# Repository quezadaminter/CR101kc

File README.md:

# CR101kc
The electrical schematics and PCB layout for the CR101 boards.  

# Firmware  
https://github.com/quezadaminter/CR101fw  

# User code  
https://github.com/quezadaminter/CR101py

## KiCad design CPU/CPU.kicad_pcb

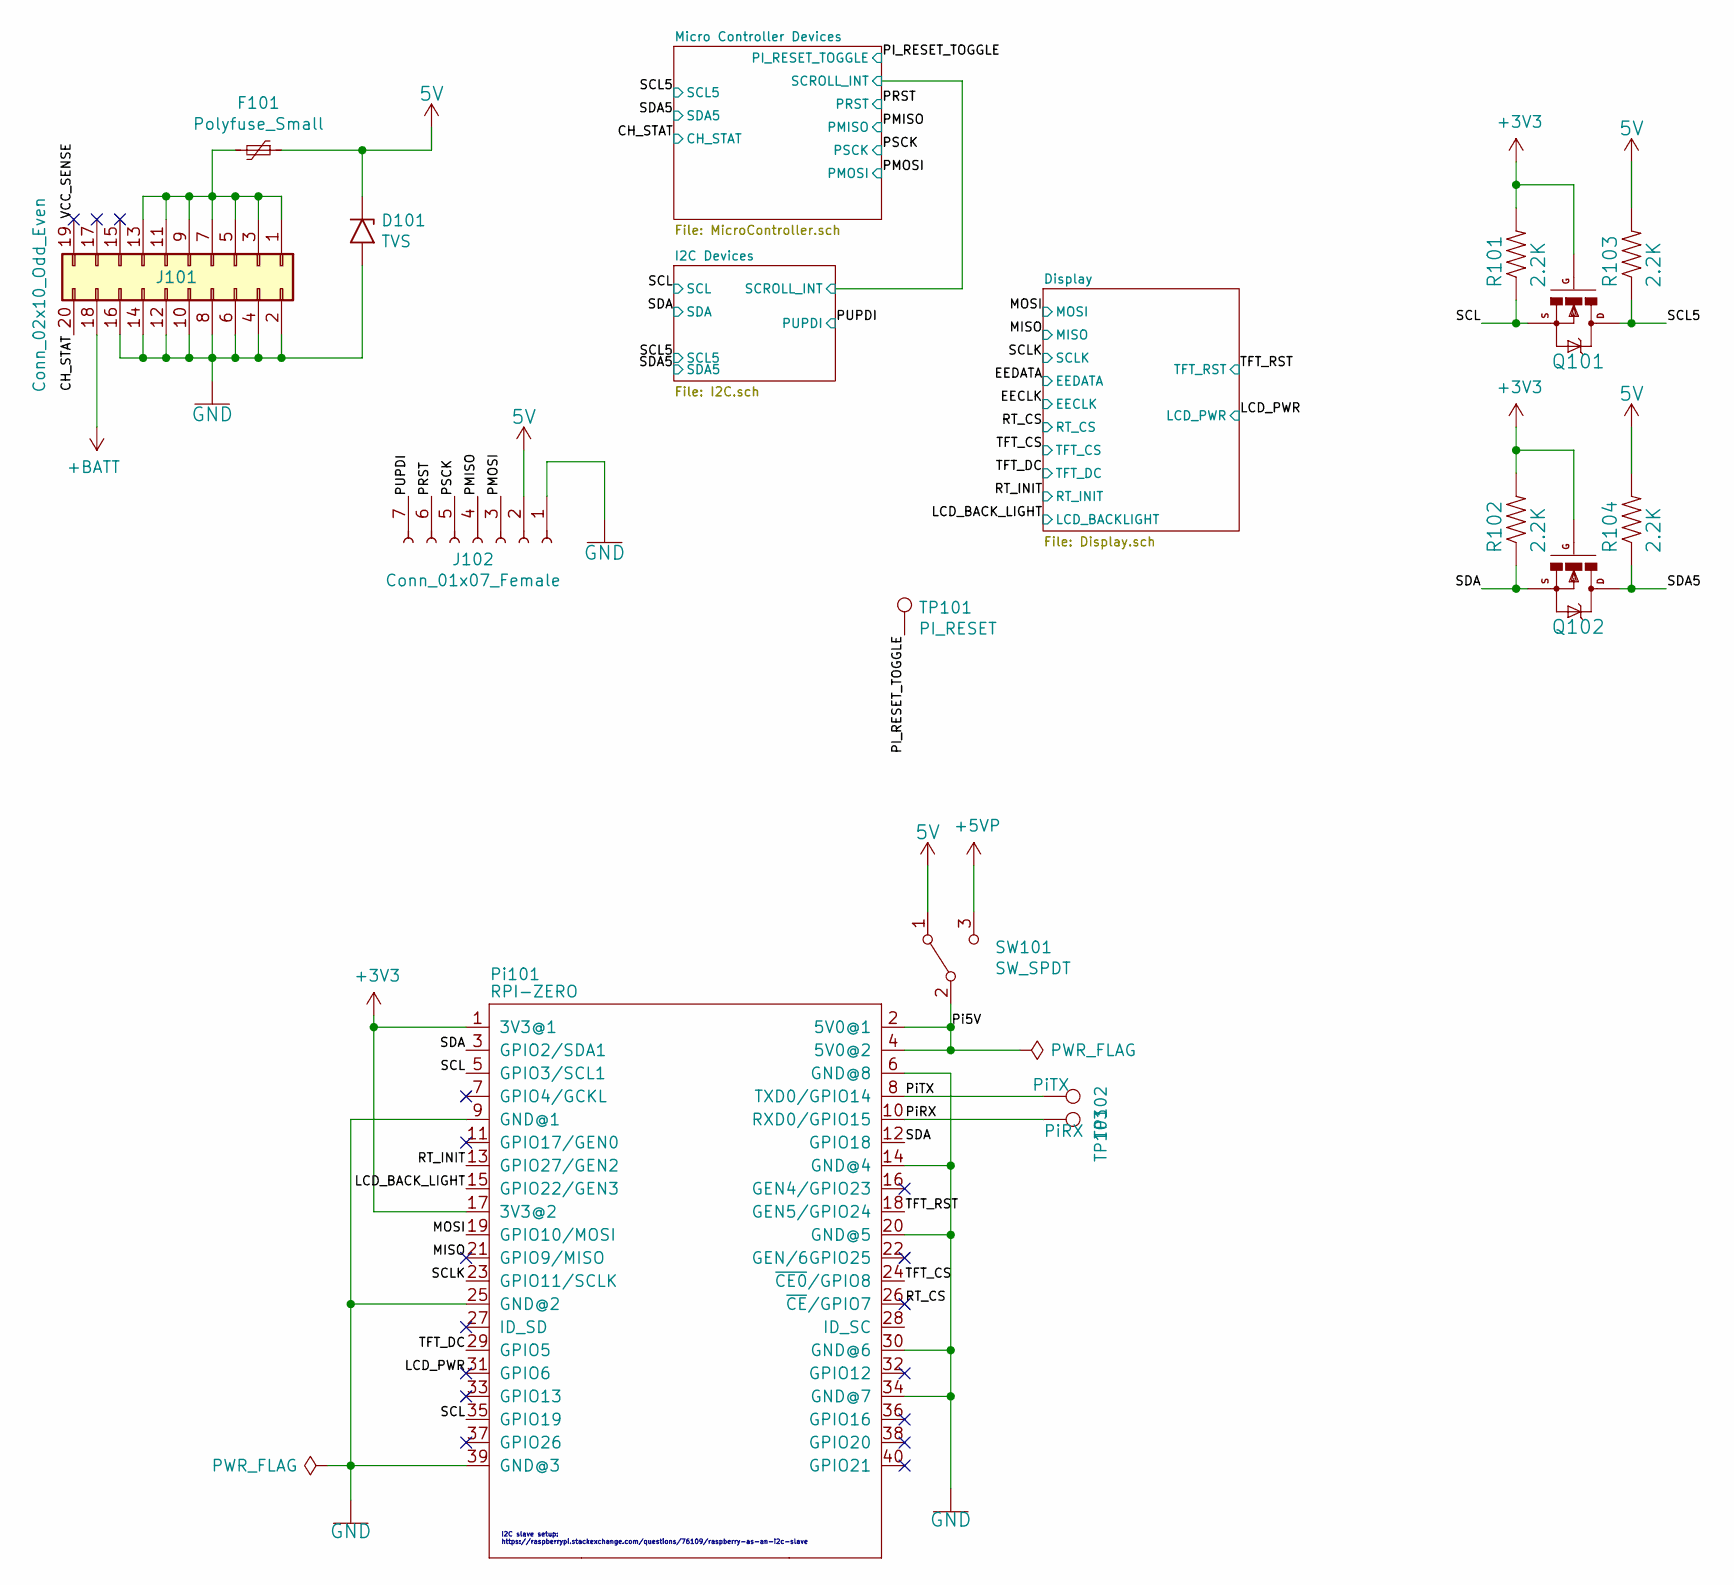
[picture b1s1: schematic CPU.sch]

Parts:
D101: TVS; D_SMB-SMC_Universal_Handsoldering; DigiKey SMBJ5V0A
F101: Polyfuse_Small; Fuse_1210_3225Metric_Pad1.42x2.65mm_HandSolder; DigiKey PTSLR12066V110
J101: Conn_02x10_Odd_Even; PinHeader_2x10_P2.00mm_Vertical_SMD; LCSC Part Number C135211
J102: Conn_01x07_Female; SM07B-SHLS-TF; DigiKey SM07B-SHLS-TF(LF)(SN)
Pi101: RPI-ZERO; RASPBERRYPI_Zero-No_Mounting_Holes_SMD_Flat; DigiKey 609-2231-ND
Q101, Q102: IRLML0040TR; SOT23; LCSC Part Number C67273
R101, R102, R103, R104: 2.2K; R_0805_2012Metric_Pad1.15x1.40mm_HandSolder; LCSC Part Number C17520
SW101: SW_SPDT; SWITCH_SS312SAH4_SPDT; LCSC Part Number C221841
TP101: PI_RESET; TestPoint_Pad_D1.0mm
TP102: PiTX; TestPoint_Pad_D1.0mm
TP103: PiRX; TestPoint_Pad_D1.0mm

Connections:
5V: D101.1 (A1), F101.1, J102.2, R103.2, R104.2, SW101.1 (A); also elsewhere on the board
+3V3: Pi101.1 (3V3@1), Pi101.17 (3V3@2), Q101.1 (G), Q102.1 (G), R101.2, R102.2; also elsewhere on the board
+5VP: SW101.3 (C); also elsewhere on the board
+BATT: J101.18; also elsewhere on the board
/CH_STAT: J101.20; also elsewhere on the board
/LCD_BACK_LIGHT: Pi101.15 (GPIO22/GEN3); also elsewhere on the board
/LCD_PWR: Pi101.31 (GPIO6)
/MISO: Pi101.21 (GPIO9/MISO)
/MOSI: Pi101.19 (GPIO10/MOSI); also elsewhere on the board
/PI_RESET_TOGGLE: TP101.1; also elsewhere on the board
/PMISO: J102.4; also elsewhere on the board
/PMOSI: J102.3; also elsewhere on the board
/PRST: J102.6; also elsewhere on the board
/PSCK: J102.5; also elsewhere on the board
/PUPDI: J102.7; also elsewhere on the board
/Pi5V: Pi101.2 (5V0@1), Pi101.4 (5V0@2), SW101.2 (B)
/PiRX: Pi101.10 (RXD0/GPIO15), TP103.1
/PiTX: Pi101.8 (TXD0/GPIO14), TP102.1
/RT_CS: Pi101.26 (~CE~/GPIO7)
/RT_INIT: Pi101.13 (GPIO27/GEN2)
/SCL: Pi101.5 (GPIO3/SCL1), Pi101.35 (GPIO19), Q101.2 (S), R101.1; also elsewhere on the board
/SCL5: Q101.3 (D), R103.1; also elsewhere on the board
/SCLK: Pi101.23 (GPIO11/SCLK); also elsewhere on the board
/SDA: Pi101.3 (GPIO2/SDA1), Pi101.12 (GPIO18), Q102.2 (S), R102.1; also elsewhere on the board
/SDA5: Q102.3 (D), R104.1; also elsewhere on the board
/TFT_CS: Pi101.24 (~CE0~/GPIO8); also elsewhere on the board
/TFT_DC: Pi101.29 (GPIO5); also elsewhere on the board
/TFT_RST: Pi101.18 (GEN5/GPIO24); also elsewhere on the board
/VCC_SENSE: J101.19
GND: D101.2 (A2), J101.2, J101.4, J101.6, J101.8, J101.10, J101.12, J101.14, J101.16, J102.1, Pi101.6 (GND@8), Pi101.9 (GND@1), Pi101.14 (GND@4), Pi101.20 (GND@5), Pi101.25 (GND@2), Pi101.30 (GND@6), Pi101.34 (GND@7), Pi101.39 (GND@3); also elsewhere on the board
unnamed: F101.2, J101.1, J101.3, J101.5, J101.7, J101.9, J101.11, J101.13

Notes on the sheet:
I2C slave setup: https://raspberrypi.stackexchange.com/questions/76109/raspberry-as-an-i2c-slave

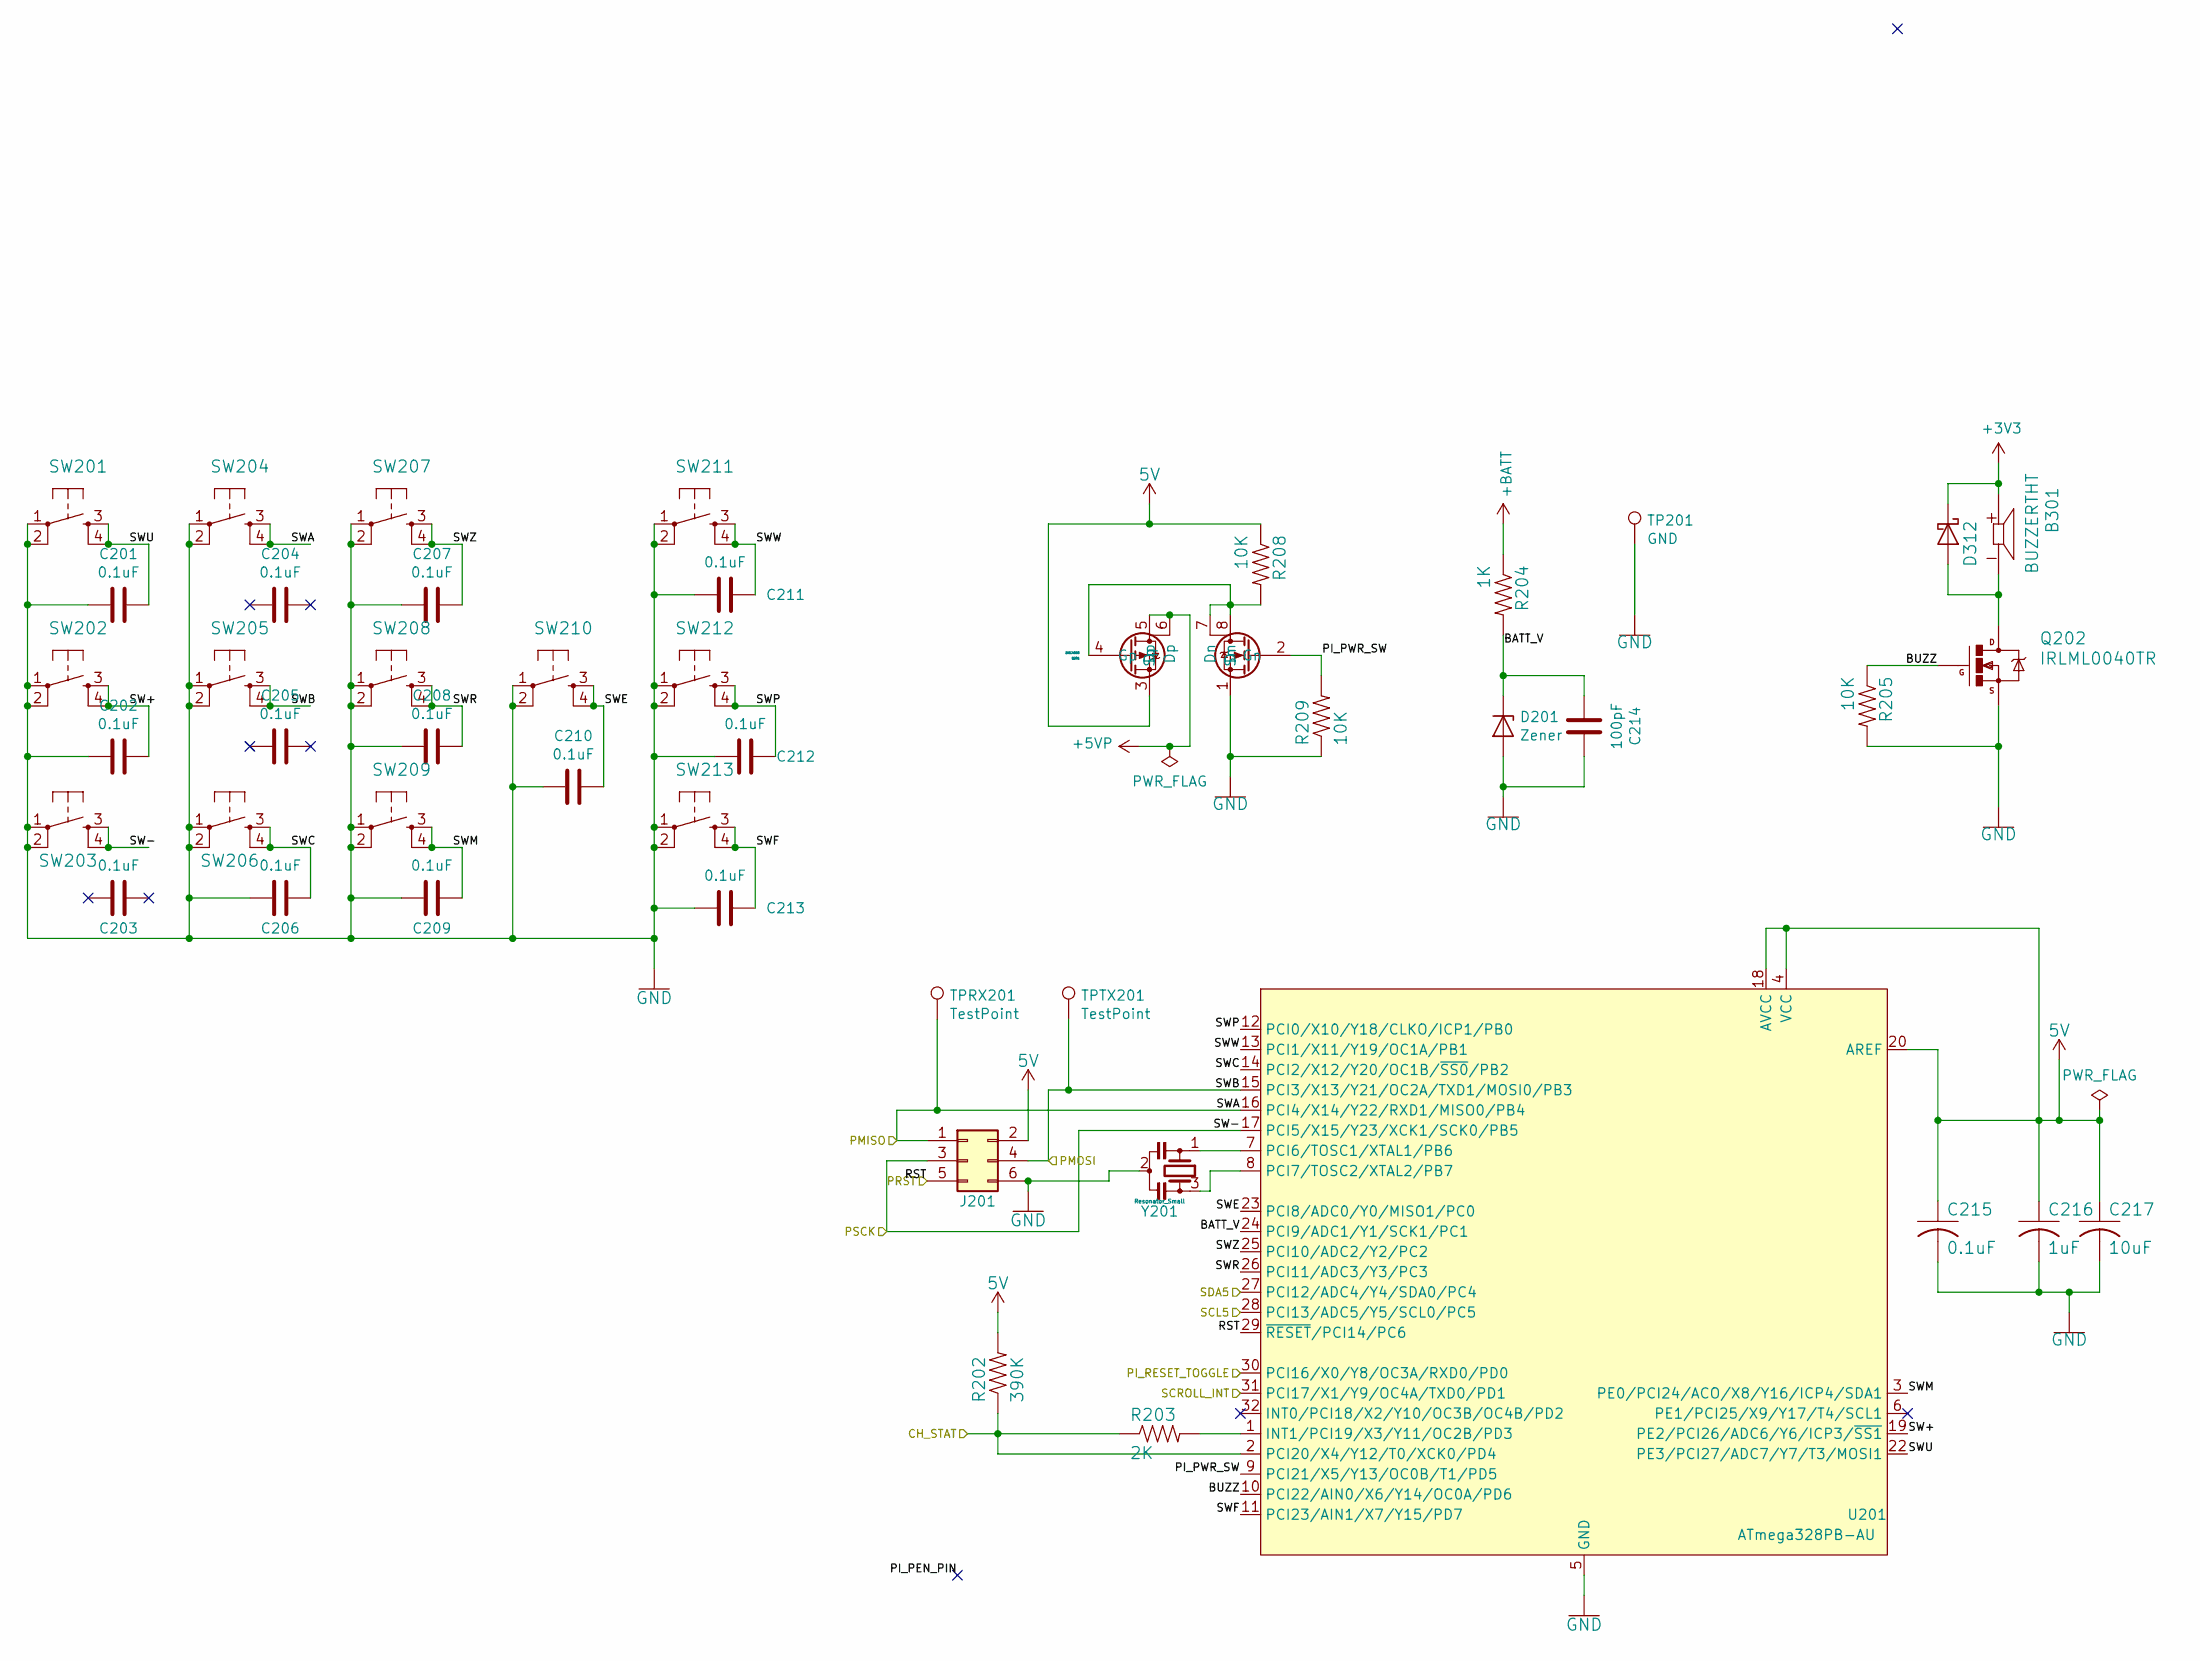
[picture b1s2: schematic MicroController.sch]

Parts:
B301: BUZZERTHT; XDCR_CMT-0904-85T; DigiKey CMT-0904-85T
C201, C202, C203, C204, C205, C206, C207, C208, C209, C210, C211, C212, C213, C215: 0.1uF; C_0805_2012Metric_Pad1.15x1.40mm_HandSolder; LCSC Part Number C49678
C214: 100pF; C_0805_2012Metric_Pad1.15x1.40mm_HandSolder; LCSC Part Number C1790
C216: 1uF; C_0805_2012Metric_Pad1.15x1.40mm_HandSolder; LCSC Part Number C28323
C217: 10uF; C_0805_2012Metric_Pad1.15x1.40mm_HandSolder; LCSC Part Number C15850
D201: Zener; D_0805_2012Metric_Pad1.15x1.40mm_HandSolder; DigiKey UDZVFHTE-174.7BCT-ND
D312: DIODE; MICRO_SMP; LCSC Part Number C111315
J201: Conn_02x03_Odd_Even; PinHeader_2x03_P2.54mm_Vertical; DigiKey 818-22-006-10-002101
Q201: DMC4050; SO-8_3.9x4.9mm_P1.27mm; DigiKey DMC4050SSD-13
Q202: IRLML0040TR; SOT23; LCSC Part Number C67273
R202: 390K; R_0805_2012Metric_Pad1.15x1.40mm_HandSolder; LCSC Part Number C17656
R203: 2K; R_0805_2012Metric_Pad1.15x1.40mm_HandSolder; LCSC Part Number C17604
R204: 1K; R_0805_2012Metric_Pad1.15x1.40mm_HandSolder; LCSC Part Number C17513
R205, R208, R209: 10K; R_0805_2012Metric_Pad1.15x1.40mm_HandSolder; LCSC Part Number C17414
SW201, SW202, SW203, SW204, SW205, SW206, SW207, SW208, SW209, SW210, SW211, SW212, SW213: TACTILE_SWITCHPTS540-SMD; PTS540-ULTRA_LOW_PROFILE_SW_SPST; LCSC Part Number C221864
TP201: GND; TestPoint_Pad_4.0x4.0mm
TPRX201: TestPoint; TestPoint_Pad_D2.0mm
TPTX201: TestPoint; TestPoint_Pad_D2.0mm
U201: ATmega328PB-AU; TQFP-32_7x7mm_P0.8mm; LCSC Part Number C132230
Y201: Resonator_Small; Resonator_SMD_muRata_CSTxExxV-3Pin_3.0x1.1mm_HandSoldering; DigiKey CSTNE20M0VH3L000R0

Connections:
5V: C215.1, C216.1, C217.1, J201.2, Q201.3 (Sp), R202.2, R208.1, U201.4 (VCC), U201.18 (AVCC), U201.20 (AREF); also elsewhere on the board
+3V3: B301.P, D312.1 (K); also elsewhere on the board
+5VP: Q201.5 (Dp), Q201.6 (Dp); also elsewhere on the board
+BATT: R204.1; also elsewhere on the board
/CH_STAT: R202.1, R203.1, U201.2 (PCI20/X4/Y12/T0/XCK0/PD4); also elsewhere on the board
/I2C Devices/SCROLL_INT: U201.31 (PCI17/X1/Y9/OC4A/TXD0/PD1); also elsewhere on the board
/Micro Controller Devices/BATT_V: C214.1, D201.1 (K), R204.2, U201.24 (PCI9/ADC1/Y1/SCK1/PC1)
/Micro Controller Devices/BUZZ: Q202.1 (G), R205.1, U201.10 (PCI22/AIN0/X6/Y14/OC0A/PD6)
/Micro Controller Devices/PI_PWR_SW: Q201.2 (Gn), R209.2, U201.9 (PCI21/X5/Y13/OC0B/T1/PD5)
/Micro Controller Devices/SW+: C202.2, SW202.3, SW202.4, U201.19 (PE2/PCI26/ADC6/Y6/ICP3/~SS1~)
/Micro Controller Devices/SWC: C206.2, SW206.3, SW206.4, U201.14 (PCI2/X12/Y20/OC1B/~SS0~/PB2)
/Micro Controller Devices/SWE: C210.2, SW210.3, SW210.4, U201.23 (PCI8/ADC0/Y0/MISO1/PC0)
/Micro Controller Devices/SWF: C213.2, SW213.3, SW213.4, U201.11 (PCI23/AIN1/X7/Y15/PD7)
/Micro Controller Devices/SWM: C209.2, SW209.3, SW209.4, U201.3 (PE0/PCI24/ACO/X8/Y16/ICP4/SDA1)
/Micro Controller Devices/SWP: C212.2, SW212.3, SW212.4, U201.12 (PCI0/X10/Y18/CLKO/ICP1/PB0)
/Micro Controller Devices/SWR: C208.2, SW208.3, SW208.4, U201.26 (PCI11/ADC3/Y3/PC3)
/Micro Controller Devices/SWU: C201.2, SW201.3, SW201.4, U201.22 (PE3/PCI27/ADC7/Y7/T3/MOSI1)
/Micro Controller Devices/SWW: C211.2, SW211.3, SW211.4, U201.13 (PCI1/X11/Y19/OC1A/PB1)
/Micro Controller Devices/SWZ: C207.2, SW207.3, SW207.4, U201.25 (PCI10/ADC2/Y2/PC2)
/PI_RESET_TOGGLE: U201.30 (PCI16/X0/Y8/OC3A/RXD0/PD0); also elsewhere on the board
/PMISO: J201.1, SW204.3, SW204.4, TPRX201.1, U201.16 (PCI4/X14/Y22/RXD1/MISO0/PB4); also elsewhere on the board
/PMOSI: J201.4, SW205.3, SW205.4, TPTX201.1, U201.15 (PCI3/X13/Y21/OC2A/TXD1/MOSI0/PB3); also elsewhere on the board
/PRST: J201.5, U201.29 (~RESET~/PCI14/PC6); also elsewhere on the board
/PSCK: J201.3, SW203.3, SW203.4, U201.17 (PCI5/X15/Y23/XCK1/SCK0/PB5); also elsewhere on the board
/SCL5: U201.28 (PCI13/ADC5/Y5/SCL0/PC5); also elsewhere on the board
/SDA5: U201.27 (PCI12/ADC4/Y4/SDA0/PC4); also elsewhere on the board
GND: C201.1, C202.1, C206.1, C207.1, C208.1, C209.1, C210.1, C211.1, C212.1, C213.1, C214.2, C215.2, C216.2, C217.2, D201.2 (A), J201.6, Q201.1 (Sn), Q202.2 (S), R205.2, R209.1, SW201.1, SW201.2, SW202.1, SW202.2, SW203.1, SW203.2, SW204.1, SW204.2, SW205.1, SW205.2, SW206.1, SW206.2, SW207.1, SW207.2, SW208.1, SW208.2, SW209.1, SW209.2, SW210.1, SW210.2, SW211.1, SW211.2, SW212.1, SW212.2, SW213.1, SW213.2, TP201.1, U201.5 (GND), U201.21 (GND), Y201.2; also elsewhere on the board
unnamed: B301.N, D312.2 (A), Q202.3 (D)
unnamed: Q201.4 (Gp), Q201.7 (Dn), Q201.8 (Dn), R208.2
unnamed: R203.2, U201.1 (INT1/PCI19/X3/Y11/OC2B/PD3)
unnamed: U201.7 (PCI6/TOSC1/XTAL1/PB6), Y201.1
unnamed: U201.8 (PCI7/TOSC2/XTAL2/PB7), Y201.3

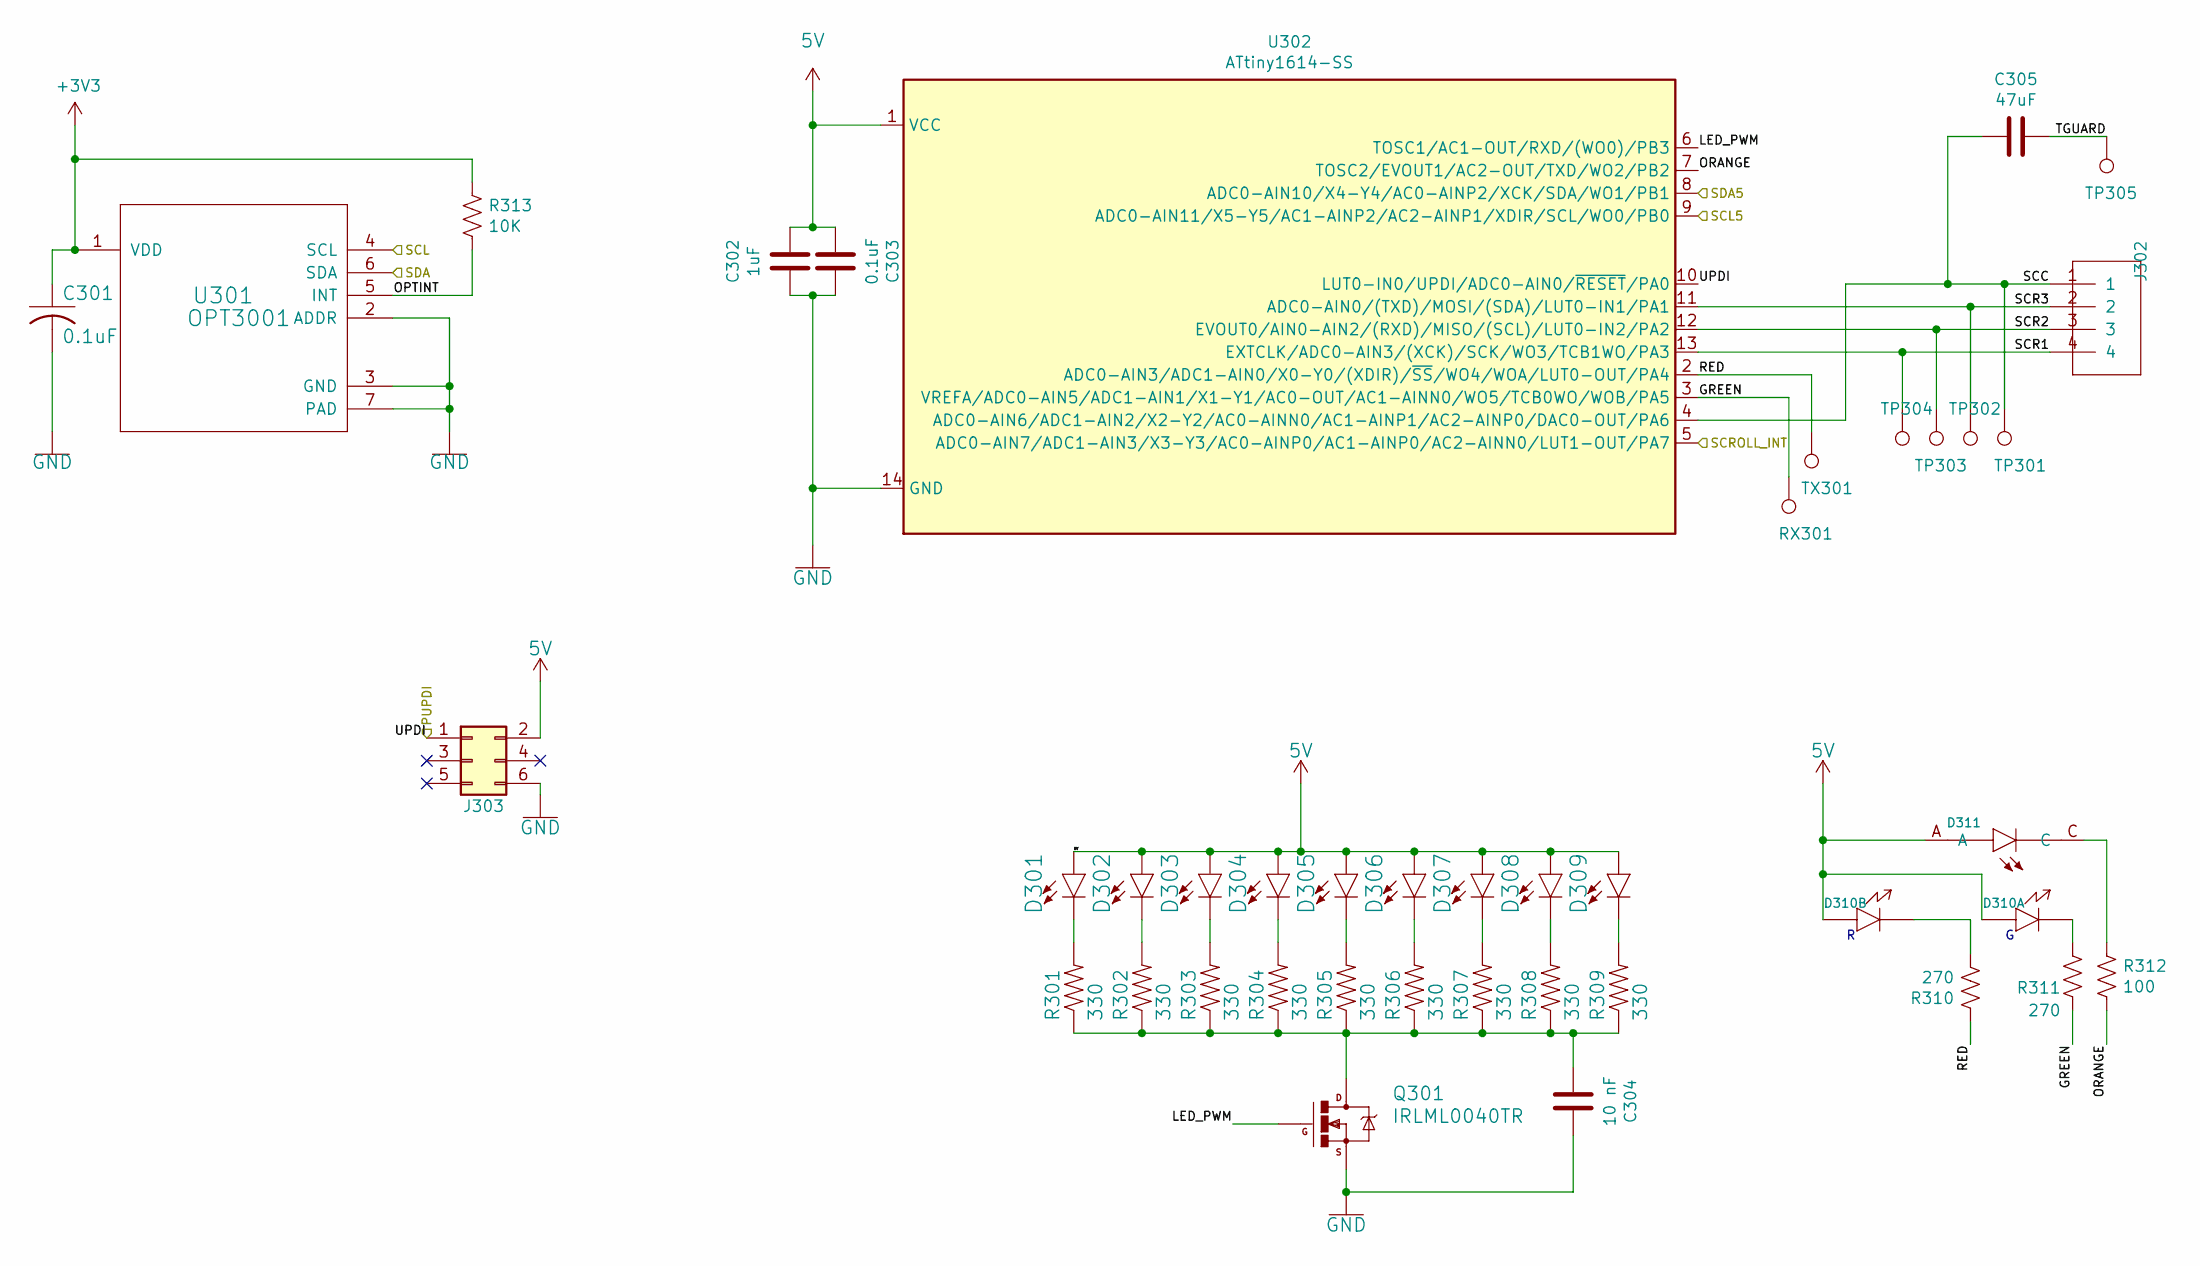
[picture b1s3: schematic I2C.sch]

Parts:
C301, C303: 0.1uF; C_0805_2012Metric_Pad1.15x1.40mm_HandSolder; LCSC Part Number C49678
C302: 1uF; C_0805_2012Metric_Pad1.15x1.40mm_HandSolder; LCSC Part Number C28323
C304: 10 nF; C_0805_2012Metric_Pad1.15x1.40mm_HandSolder; LCSC Part Number C1710
C305: 47uF; C_0805_2012Metric_Pad1.15x1.40mm_HandSolder; LCSC Part Number C28323
D301, D302, D303, D304, D305, D306, D307, D308, D309: LED0603; LED-0603; LCSC Part Number C161619
D310: RG; INOLUX_IN-S85DATRG; LCSC Part Number C391863
D311: 598-8030-107F; LEDSC160X80X70L45N; LCSC Part Number C264422
J302: 1X4SMD-FPC; KYOCERA-6227-FPC_FFC; DigiKey 046227004100829+
J303: Conn_02x03_Odd_Even; PinHeader_2x03_P2.54mm_Vertical; DigiKey 818-22-006-10-002101
Q301: IRLML0040TR; SOT23; LCSC Part Number C67273
R301, R302, R303, R304, R305, R306, R307, R308, R309: 330; R_0805_2012Metric_Pad1.15x1.40mm_HandSolder; LCSC Part Number C17630
R310, R311: 270; R_0805_2012Metric_Pad1.15x1.40mm_HandSolder; LCSC Part Number C17590
R312: 100; R_0805_2012Metric_Pad1.15x1.40mm_HandSolder; LCSC Part Number C17408
R313: 10K; R_0805_2012Metric_Pad1.15x1.40mm_HandSolder; LCSC Part Number C17414
RX301: TestPoint; TestPoint_Pad_D1.0mm
TP301, TP302, TP303, TP304: TestPoint; TestPoint_Pad_D1.0mm
TP305: TestPoint; TestPoint_Pad_D1.0mm; DigiKey 709150001030006
TX301: TestPoint; TestPoint_Pad_D1.0mm
U301: OPT3001; DNP0006A; LCSC Part Number C90462
U302: ATtiny1614-SS; SOIC-14_3.9x8.7mm_P1.27mm; LCSC Part Number C141724

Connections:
5V: C302.2, C303.1, D301.A, D302.A, D303.A, D304.A, D305.A, D306.A, D307.A, D308.A, D309.A, D310.2 (A), D310.4 (A), D311.A, J303.2, U302.1 (VCC); also elsewhere on the board
+3V3: C301.1, R313.1, U301.1 (VDD); also elsewhere on the board
/I2C Devices/GREEN: R311.2, RX301.1, U302.3 (VREFA/ADC0-AIN5/ADC1-AIN1/X1-Y1/AC0-OUT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)
/I2C Devices/LED_PWM: Q301.1 (G), U302.6 (TOSC1/AC1-OUT/RXD/(WO0)/PB3)
/I2C Devices/OPTINT: R313.2, U301.5 (INT)
/I2C Devices/ORANGE: R312.2, U302.7 (TOSC2/EVOUT1/AC2-OUT/TXD/WO2/PB2)
/I2C Devices/RED: R310.1, TX301.1, U302.2 (ADC0-AIN3/ADC1-AIN0/X0-Y0/(XDIR)/~SS~/W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)
/I2C Devices/SCC: C305.1, J302.1, TP301.1, U302.4 (ADC0-AIN6/ADC1-AIN2/X2-Y2/AC0-AINN0/AC1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)
/I2C Devices/SCR1: J302.4, TP304.1, U302.13 (EXTCLK/ADC0-AIN3/(XCK)/SCK/WO3/TCB1WO/P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)
/I2C Devices/SCR2: J302.3, TP303.1, U302.12 (EVOUT0/AIN0-AIN2/(RXD)/MISO/(SCL)/LUT0-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)
/I2C Devices/SCR3: J302.2, TP302.1, U302.11 (ADC0-AIN0/(TXD)/MOSI/(SDA)/LUT0-IN1/PA1)
/I2C Devices/SCROLL_INT: U302.5 (ADC0-AIN7/ADC1-AIN3/X3-Y3/AC0-AINP0/AC1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); also elsewhere on the board
/I2C Devices/TGUARD: C305.2, TP305.1
/PUPDI: J303.1, U302.10 (LUT0-IN0/UPDI/ADC0-AIN0/~RESET~/PA0); also elsewhere on the board
/SCL: U301.4 (SCL); also elsewhere on the board
/SCL5: U302.9 (ADC0-AIN11/X5-Y5/AC1-AINP2/AC2-AINP1/XD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); also elsewhere on the board
/SDA: U301.6 (SDA); also elsewhere on the board
/SDA5: U302.8 (ADC0-AIN10/X4-Y4/AC0-AINP2/XCK/SDA/WO1/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); also elsewhere on the board
GND: C301.2, C302.1, C303.2, C304.2, J303.6, Q301.2 (S), U301.2 (ADDR), U301.3 (GND), U301.7 (PAD), U302.14 (GND); also elsewhere on the board
unnamed: C304.1, Q301.3 (D), R301.1, R302.1, R303.1, R304.1, R305.1, R306.1, R307.1, R308.1, R309.1
unnamed: D301.C, R301.2
unnamed: D302.C, R302.2
unnamed: D303.C, R303.2
unnamed: D304.C, R304.2
unnamed: D305.C, R305.2
unnamed: D306.C, R306.2
unnamed: D307.C, R307.2
unnamed: D308.C, R308.2
unnamed: D309.C, R309.2
unnamed: D310.1 (K), R310.2
unnamed: D310.3 (K), R311.1
unnamed: D311.C, R312.1

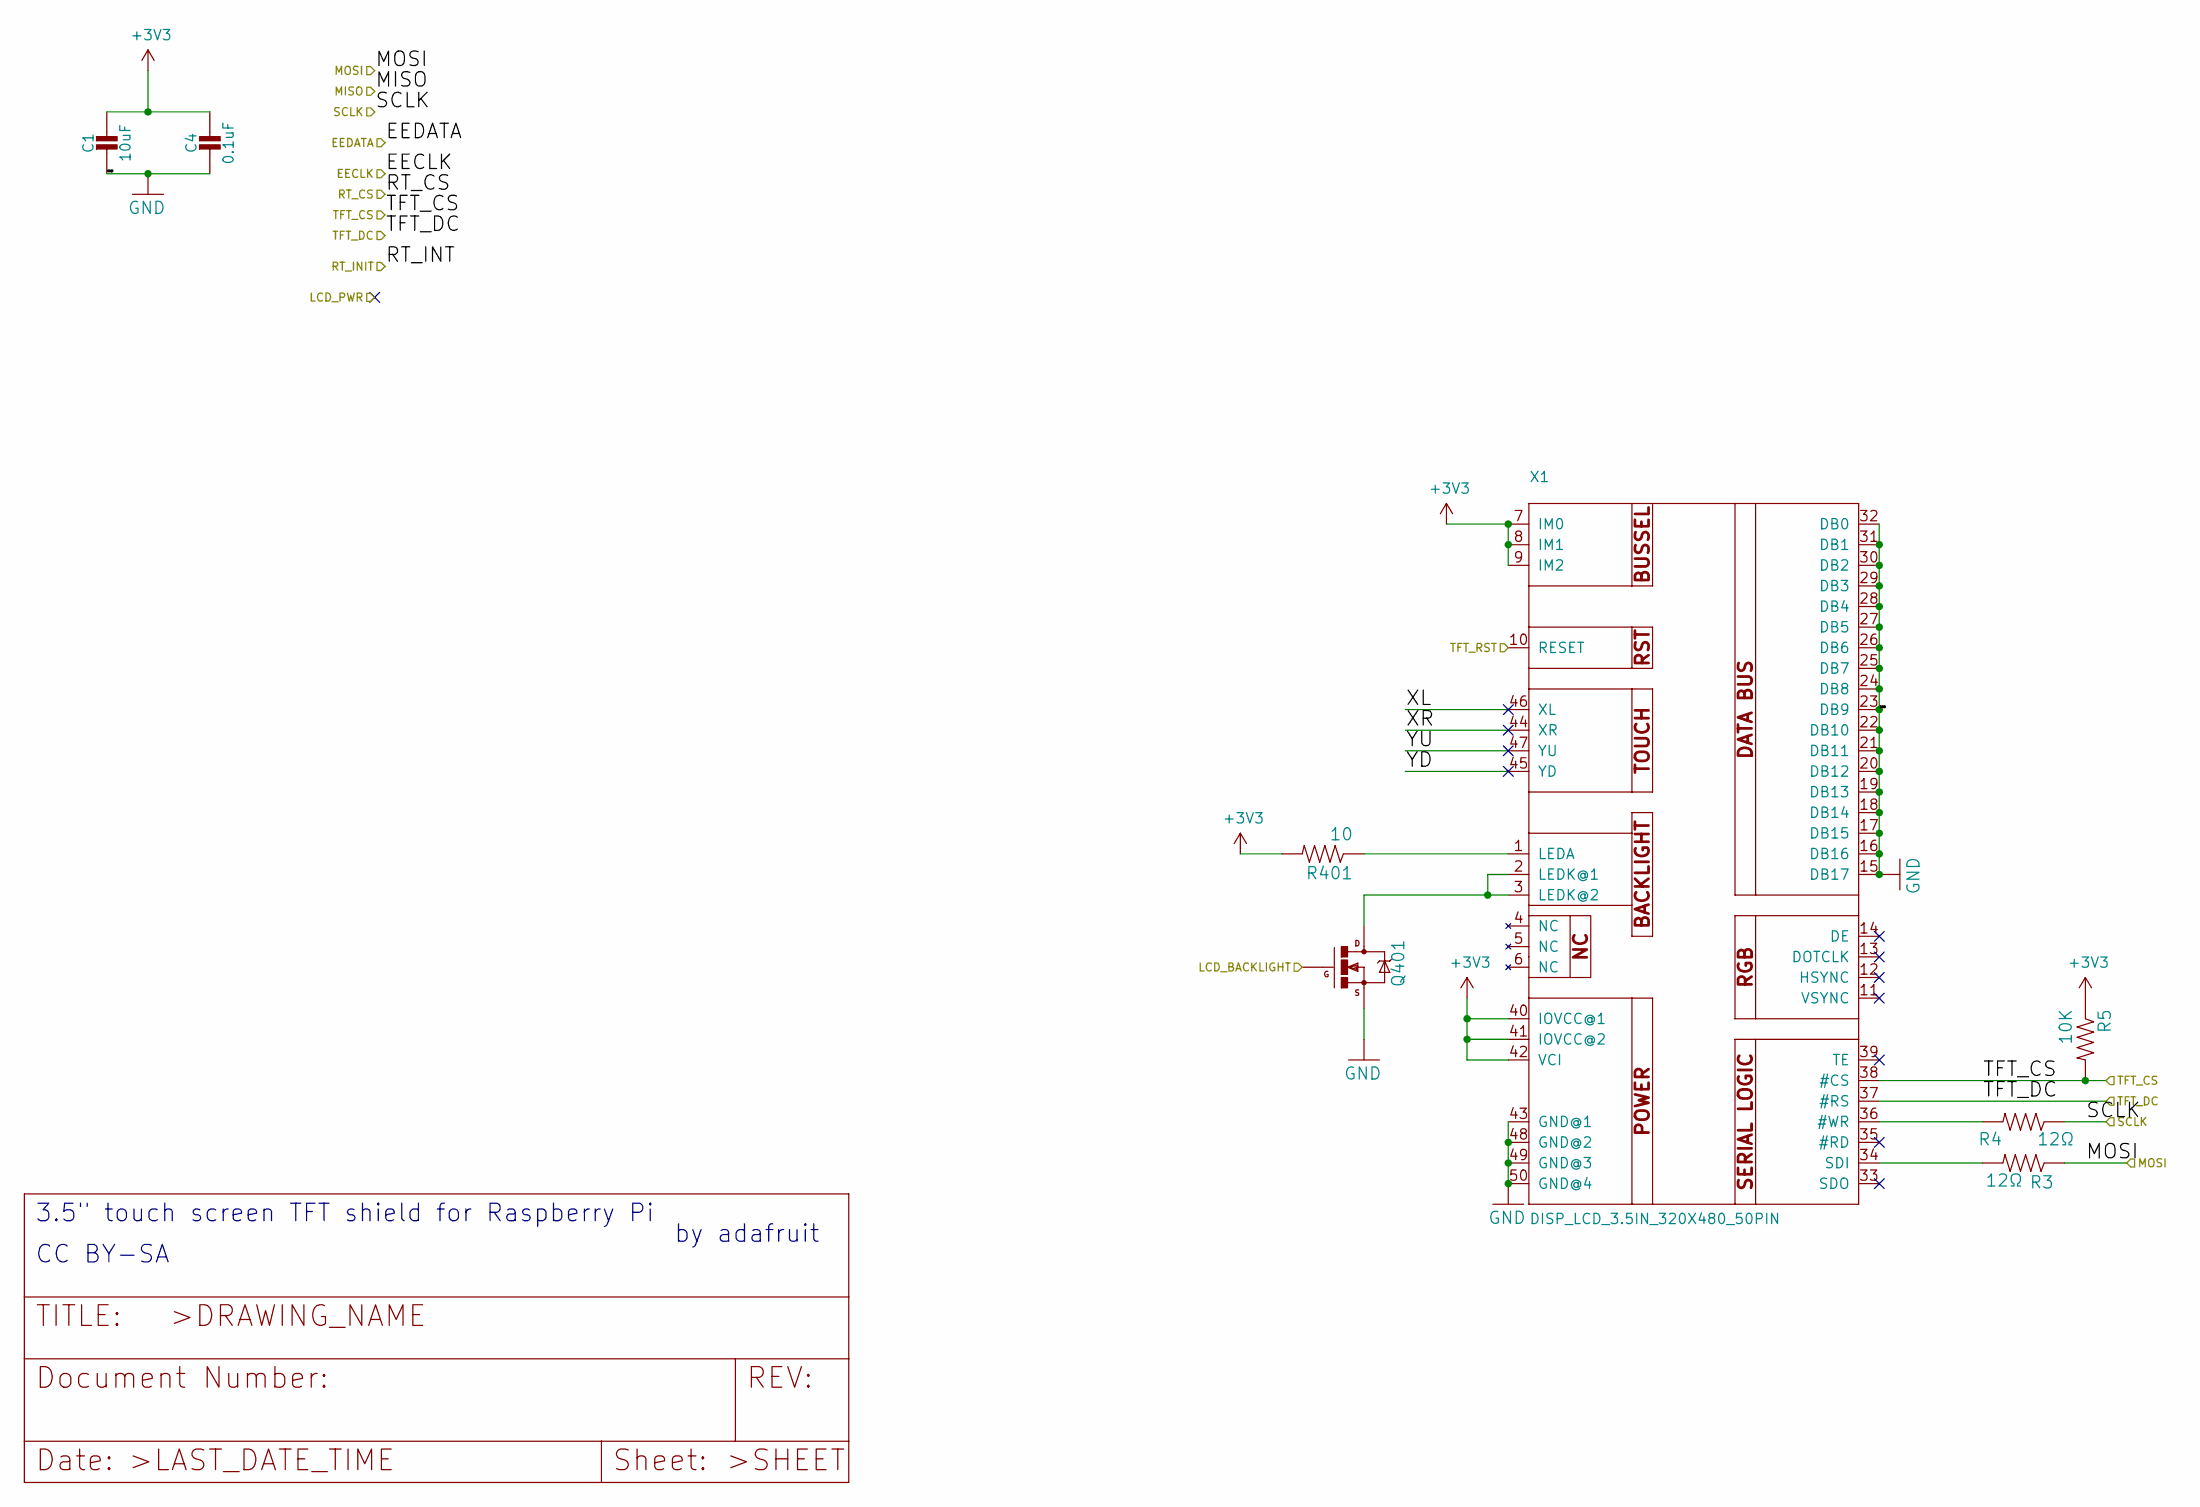
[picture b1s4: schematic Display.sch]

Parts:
C1: 10uF; C_0805_2012Metric_Pad1.15x1.40mm_HandSolder; DigiKey EMK212ABJ106MD-T
C4: 0.1uF; C_0805_2012Metric_Pad1.15x1.40mm_HandSolder; LCSC Part Number C49678
Q401: IRLML0040TR; SOT23; LCSC Part Number C67273
R3, R4: 12Ω; R_0805_2012Metric_Pad1.15x1.40mm_HandSolder; LCSC Part Number C17415
R5: 10K; R_0805_2012Metric_Pad1.15x1.40mm_HandSolder; LCSC Part Number C17414
R401: 10; R_0805_2012Metric_Pad1.15x1.40mm_HandSolder; LCSC Part Number C17415
X1: DISP_LCD_3.5IN_320X480_50PIN; TFT_3.5IN_320X480_50PIN_BUY_DISPLAY_ER-TFT035-6; DigiKey 609-1202-1-ND

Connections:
+3V3: C1.1, C4.1, R5.1, R401.2, X1.7 (IM0), X1.8 (IM1), X1.9 (IM2), X1.40 (IOVCC@1), X1.41 (IOVCC@2), X1.42 (VCI); also elsewhere on the board
/Display/XL: X1.46 (XL)
/Display/XR: X1.44 (XR)
/Display/YD: X1.45 (YD)
/Display/YU: X1.47 (YU)
/LCD_BACK_LIGHT: Q401.1 (G); also elsewhere on the board
/MOSI: R3.1; also elsewhere on the board
/SCLK: R4.1; also elsewhere on the board
/TFT_CS: R5.2, X1.38 (#CS); also elsewhere on the board
/TFT_DC: X1.37 (#RS); also elsewhere on the board
/TFT_RST: X1.10 (RESET); also elsewhere on the board
GND: C1.2, C4.2, Q401.2 (S), X1.15 (DB17), X1.16 (DB16), X1.17 (DB15), X1.18 (DB14), X1.19 (DB13), X1.20 (DB12), X1.21 (DB11), X1.22 (DB10), X1.23 (DB9), X1.24 (DB8), X1.25 (DB7), X1.26 (DB6), X1.27 (DB5), X1.28 (DB4), X1.29 (DB3), X1.30 (DB2), X1.31 (DB1), X1.32 (DB0), X1.43 (GND@1), X1.48 (GND@2), X1.49 (GND@3), X1.50 (GND@4); also elsewhere on the board
unnamed: Q401.3 (D), X1.2 (LEDK@1), X1.3 (LEDK@2)
unnamed: R3.2, X1.34 (SDI)
unnamed: R4.2, X1.36 (#WR)
unnamed: R401.1, X1.1 (LEDA)

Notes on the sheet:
3.5" touch screen TFT shield for Raspberry Pi
by adafruit~
CC BY-SA

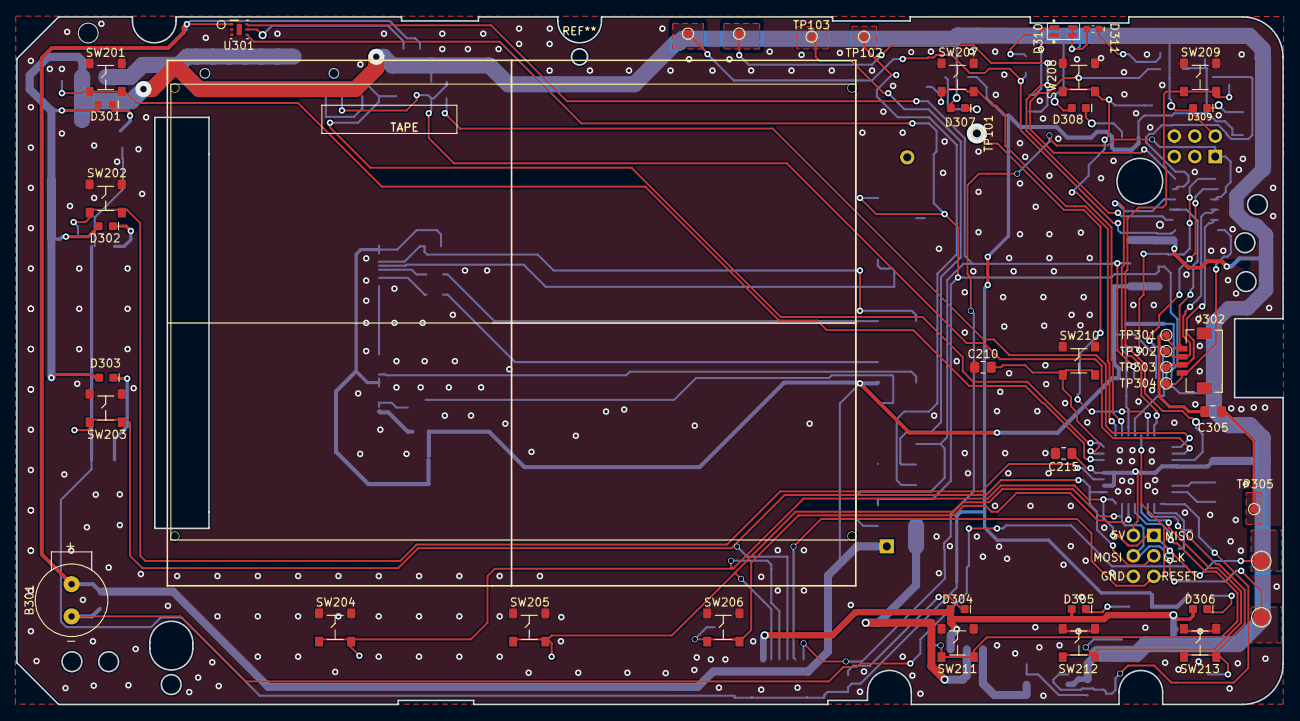
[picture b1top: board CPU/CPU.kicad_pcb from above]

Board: 2 copper layers, 157.1 x 85.3 mm, 111 parts (0 on the bottom side), 72 nets.

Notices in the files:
parts and their libraries:
Copyright 2016 Accelerated Designs. All rights reserved.
